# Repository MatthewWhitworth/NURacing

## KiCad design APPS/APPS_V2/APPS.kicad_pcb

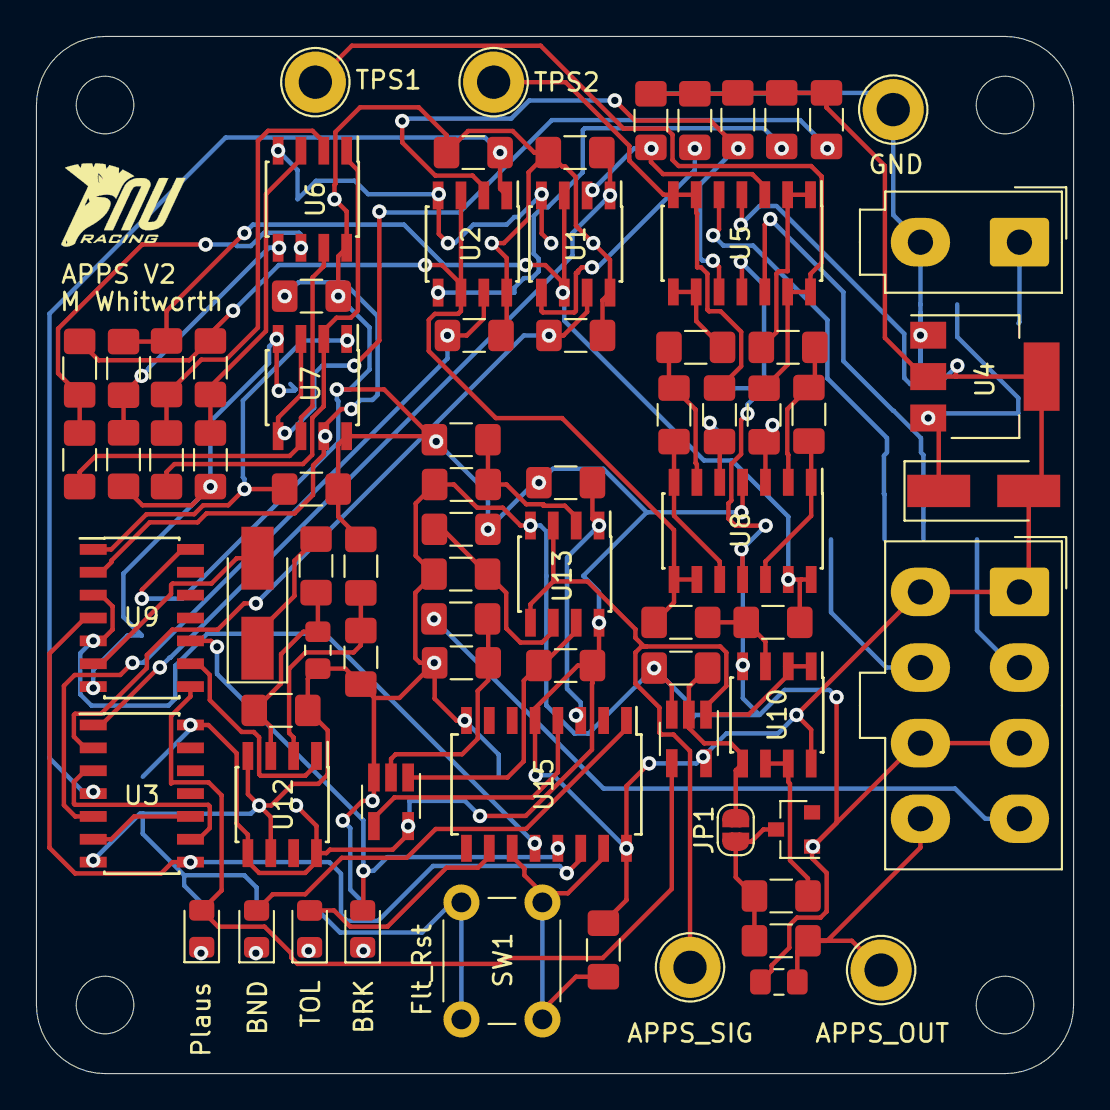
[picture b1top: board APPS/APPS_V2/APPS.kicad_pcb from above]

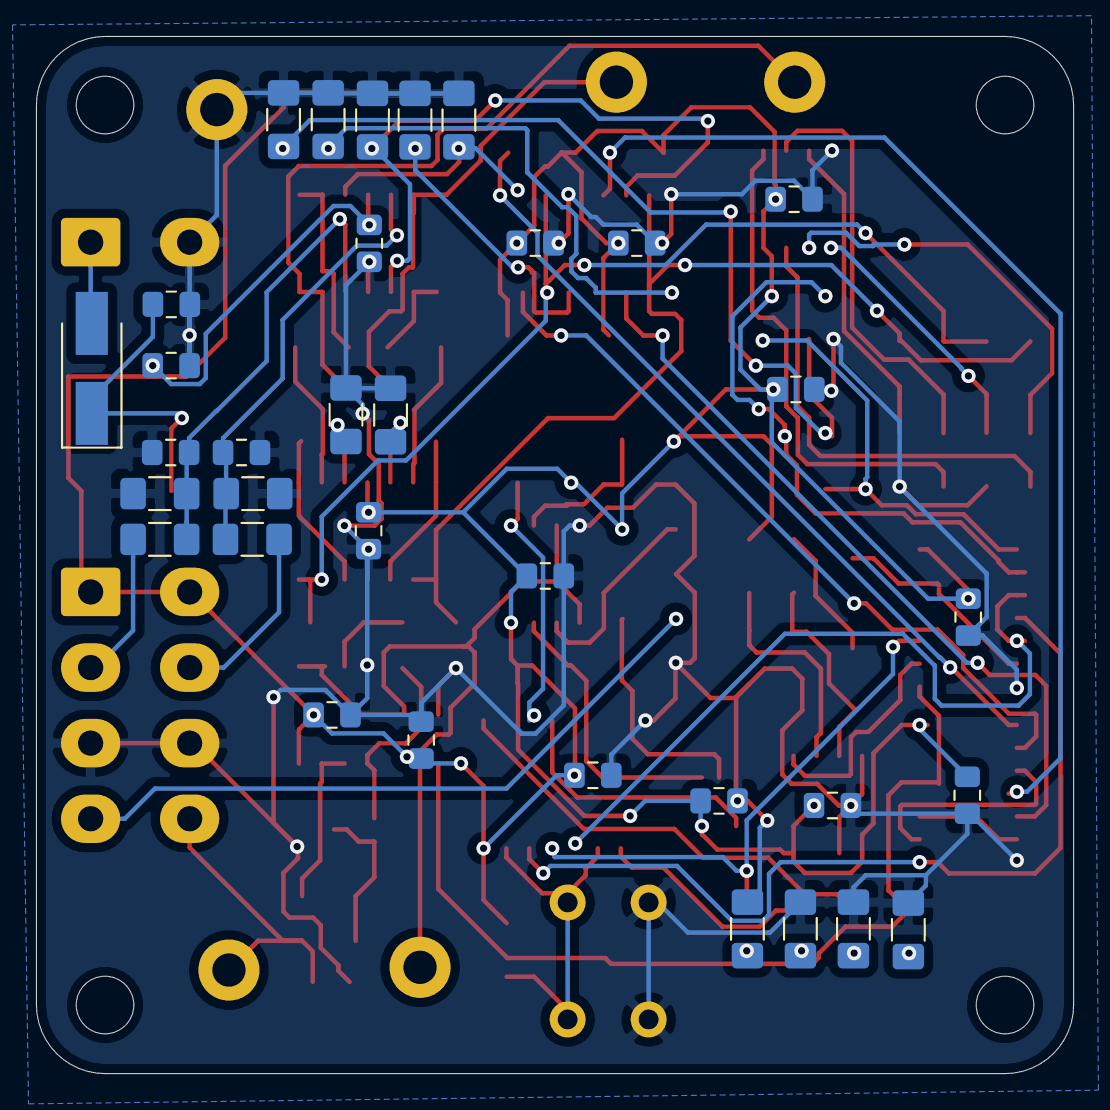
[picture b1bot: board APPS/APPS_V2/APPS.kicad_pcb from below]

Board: 2 copper layers, 57.6 x 57.6 mm, 110 parts (34 on the bottom side), 68 nets.

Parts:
C1, C2, C4, C6, C7, C8, C9, C10, C11, C12, C15, C16, C17, C18: 0.1uF; C_0805_2012Metric_Pad1.15x1.40mm_HandSolder
C3, C5: 10uF; C_0805_2012Metric_Pad1.15x1.40mm_HandSolder
C13: 2.2uF; C_0805_2012Metric_Pad1.15x1.40mm_HandSolder
C14: 47pF; C_0805_2012Metric_Pad1.15x1.40mm_HandSolder
C19, C20: C; C_0805_2012Metric_Pad1.15x1.40mm_HandSolder
D1, D2, D3: D; D_SMA_Handsoldering
D4: Plaus; LED_0805_2012Metric_Pad1.15x1.40mm_HandSolder
D6: D_Zener; D_SOT-23_ANK
D7: BRK; LED_0805_2012Metric_Pad1.15x1.40mm_HandSolder
D8: TOL; LED_0805_2012Metric_Pad1.15x1.40mm_HandSolder
D9: BND; LED_0805_2012Metric_Pad1.15x1.40mm_HandSolder
J1: Conn_01x08_Female; Molex_Mini-Fit_Jr_5566-08A_2x04_P4.20mm_Vertical
J2: Conn_01x02_Female; Molex_Mini-Fit_Jr_5566-02A_2x01_P4.20mm_Vertical
JP1: SolderJumper_2_Open; SolderJumper-2_P1.3mm_Open_RoundedPad1.0x1.5mm
R1, R2, R3, R4, R5, R6, R11, R12, R13, R14, R31, R47, R48, R49, R50: R; R_1206_3216Metric_Pad1.42x1.75mm_HandSolder
R7, R8, R9, R10, R15, R16, R17, R18, R19, R20, R21, R22, R23, R24, R25, R26, R30, R40, R41, R46: 10k; R_1206_3216Metric_Pad1.42x1.75mm_HandSolder
R27: 2k; R_1206_3216Metric_Pad1.42x1.75mm_HandSolder
R28, R35: 20k; R_1206_3216Metric_Pad1.42x1.75mm_HandSolder
R29: 100k; R_1206_3216Metric_Pad1.42x1.75mm_HandSolder
R32: 330; R_1206_3216Metric_Pad1.42x1.75mm_HandSolder
R33, R43, R44, R45: 470; R_1206_3216Metric_Pad1.42x1.75mm_HandSolder
R34: 10; R_1206_3216Metric_Pad1.42x1.75mm_HandSolder
R36: 3k; R_1206_3216Metric_Pad1.42x1.75mm_HandSolder
R37: 1.05k; R_1206_3216Metric_Pad1.42x1.75mm_HandSolder
R38: 1k; R_1206_3216Metric_Pad1.42x1.75mm_HandSolder
R39: 6.8k; R_1206_3216Metric_Pad1.42x1.75mm_HandSolder
R42: 4.7k; R_1206_3216Metric_Pad1.42x1.75mm_HandSolder
Rc1, Rc2: R; R_1206_3216Metric_Pad1.42x1.75mm_HandSolder
Rd1, Rd2: R; R_1206_3216Metric_Pad1.42x1.75mm_HandSolder
Re1, Re2: R; R_1206_3216Metric_Pad1.42x1.75mm_HandSolder
Rf1, Rf2: R; R_1206_3216Metric_Pad1.42x1.75mm_HandSolder
SW1: Flt_Rst; SW_PUSH_6mm
TP1: TPS1; TestPoint_Loop_D2.50mm_Drill1.85mm
TP2: TPS2; TestPoint_Loop_D2.50mm_Drill1.85mm
TP3: APPS_SIG; TestPoint_Loop_D2.50mm_Drill1.85mm
TP4: APPS_OUT; TestPoint_Loop_D2.50mm_Drill1.85mm
TP5: GND; TestPoint_Loop_D2.50mm_Drill1.85mm
U1, U2, U7, U13: LM393; SOIC-8_3.9x4.9mm_P1.27mm
U3, U9: 74LS08; SOIC-14_3.9x8.7mm_P1.27mm
U4: AP1117-50; SOT-223-3_TabPin2
U5, U8: MCP6004; SOIC-14_3.9x8.7mm_P1.27mm
U6, U10, U12: MCP6002-xSN; SOIC-8_3.9x4.9mm_P1.27mm
U11: Analog_Switch; SOT-23-5_HandSoldering
U14: 74LVC1G00; SOT-23-5_HandSoldering
U15: CD4044B; SOIC-16W_5.3x10.2mm_P1.27mm

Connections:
+12V: C3.1, D1.1, D2.1, U4.3
/APPS_OUT: C14.1, J1.8, R34.1, TP4.1
/APPS_SIG: TP3.1, U10.1, U10.2, U11.1, U13.3, U13.5
/BND_FLT: U3.8, U9.4, U15.14
/BRK_FLT: D7.2, U9.10, U15.13
/BRK_IN: J1.4, R39.2
/TOL_FLT: U9.3, U9.5, U15.12
/TPS_1: R16.2, R17.2, R25.2, U1.3, U1.6, U8.13, U8.14
/TPS_1_IN: J1.2, R48.2
/TPS_2: R15.2, R18.2, R26.2, U2.3, U2.6, U8.8, U8.9
/TPS_2_IN: J1.6, R47.2
/Tolerance: R13.2, R14.1, U7.3, U7.5
/Vmax_1: R3.2, R4.1, U1.5
/Vmax_2: R11.2, R12.1, U2.5
/Vmin_1: R1.2, R2.1, U1.2, U5.3
/Vmin_2: R5.2, R6.1, U2.2, U5.10
GND: C1.2, C2.2, C3.2, C4.2, C5.2, C6.2, C7.2, C8.2, C9.2, C10.2, C11.2, C12.2, C13.2, C14.2, C15.2, C16.2, C17.2, C18.2, C19.2, C20.2, D6.2, J1.3, J1.7, J2.2, R2.2, R4.2, R6.2, R12.2, R14.2, R19.2, R20.2, R28.1, R30.2, R31.2, R33.1, R37.2, R38.2, R42.2, R43.1, R44.1, R45.2, R49.2, R50.2, Rc1.1, Rc2.1, SW1.2, TP5.1, U1.4, U2.4, U3.7, U4.1, U5.11, U6.4, U7.4, U8.11, U9.7, U10.4, U11.3, U12.4, U12.6, U13.4, U14.3, U15.8
unnamed: C13.1, R27.1, R28.2, U12.3
unnamed: C19.1, R47.1, R49.1, U5.5
unnamed: C20.1, R48.1, R50.1, U5.12
unnamed: D1.2, J2.1
unnamed: D3.1, R27.2
unnamed: D3.2, U9.6
unnamed: D4.1, R33.2
unnamed: D4.2, U9.8, U11.4
unnamed: D6.1, JP1.2, R32.1, R34.2
unnamed: D7.1, R43.2
unnamed: D8.1, R44.2
unnamed: D8.2, U15.10
unnamed: D9.1, R45.1
unnamed: D9.2, U15.1
unnamed: JP1.1, R31.1, U10.5, U11.2
unnamed: R7.2, U1.1, U3.1
unnamed: R8.1, U1.7, U3.2
unnamed: R9.2, U2.1, U3.4
unnamed: R10.2, U2.7, U3.5
unnamed: R15.1, R19.1, U6.3
unnamed: R16.1, R21.1, U6.2
unnamed: R17.1, R20.1, U6.5
unnamed: R18.1, R22.1, U6.6
unnamed: R21.2, U6.1, U7.2
unnamed: R22.2, U6.7, U7.6
unnamed: R23.2, U7.1, U9.1
unnamed: R24.1, U7.7, U9.2
unnamed: R25.1, R26.1, U10.3
unnamed: R29.1, R30.1, U12.2
unnamed: R32.2, U10.6, U10.7
unnamed: R35.1, R37.1, U13.2
unnamed: R36.1, R38.1, U13.6
unnamed: R39.1, R42.1, U14.2
unnamed: R40.2, U13.1, U15.3
unnamed: R41.2, U13.7, U14.1
unnamed: R46.1, SW1.1, U15.11, U15.15
unnamed: Rc1.2, Rd1.1, U8.3
unnamed: Rc2.2, Rd2.1, U8.5
unnamed: Rd1.2, TP1.1, U5.13, U5.14
unnamed: Rd2.2, TP2.1, U5.6, U5.7
unnamed: Re1.1, U5.1, U5.2
unnamed: Re1.2, Rf1.1, U8.2
unnamed: Re2.1, U5.8, U5.9
unnamed: Re2.2, Rf2.1, U8.6
unnamed: Rf1.2, U8.1, U8.12
unnamed: Rf2.2, U8.7, U8.10
unnamed: U3.3, U3.9
unnamed: U3.6, U3.10
unnamed: U9.9, U12.1
unnamed: U14.4, U15.4
VCC: C1.1, C2.1, C4.1, C5.1, C6.1, C7.1, C8.1, C9.1, C10.1, C11.1, C12.1, C15.1, C16.1, C17.1, C18.1, D2.2, J1.1, J1.5, R1.1, R3.1, R5.1, R7.1, R8.2, R9.1, R10.1, R11.1, R13.1, R23.1, R24.2, R29.2, R35.2, R36.2, R40.1, R41.1, R46.2, U1.8, U2.8, U3.14, U4.2, U5.4, U6.8, U7.8, U8.4, U9.14, U10.8, U11.5, U12.5, U12.8, U13.8, U14.5, U15.5, U15.16

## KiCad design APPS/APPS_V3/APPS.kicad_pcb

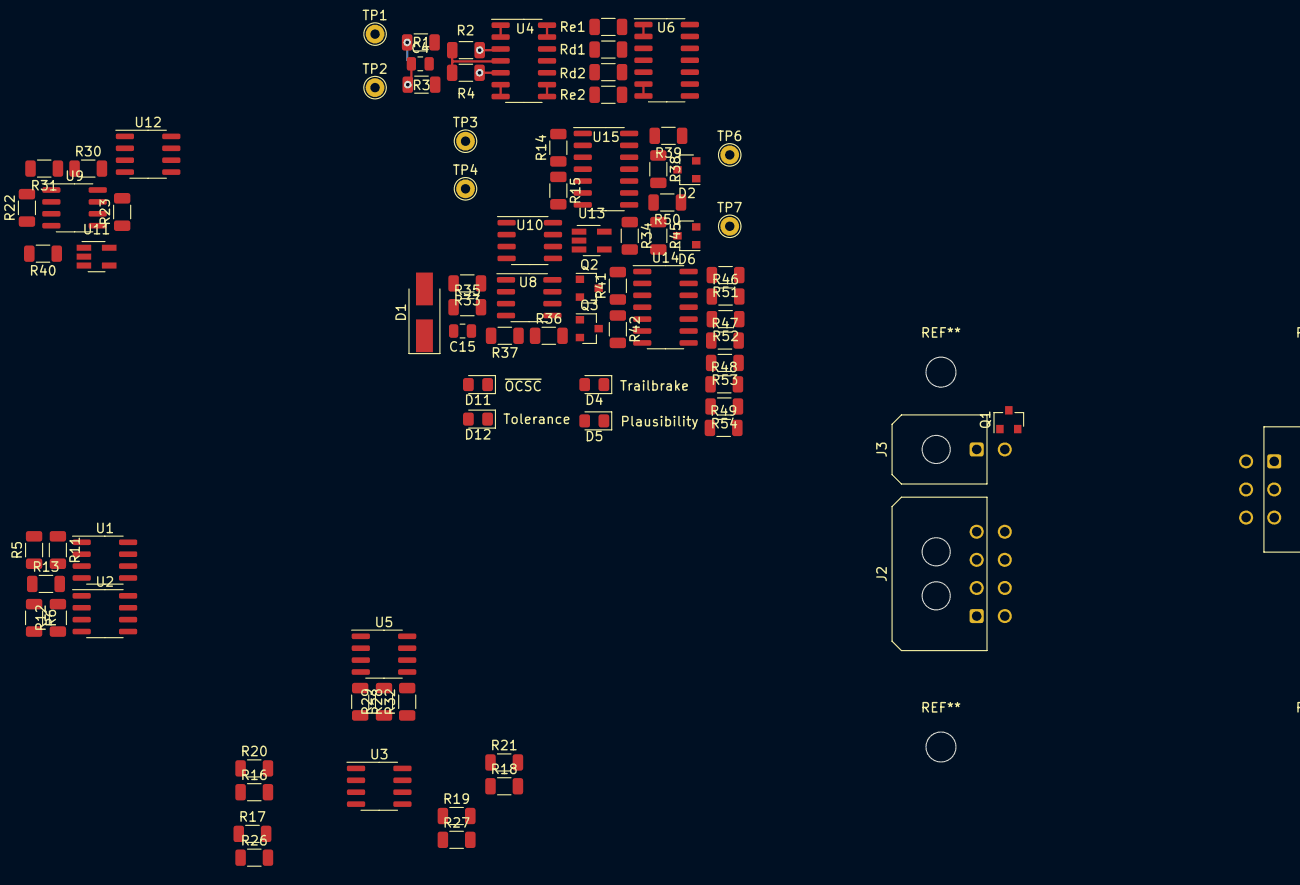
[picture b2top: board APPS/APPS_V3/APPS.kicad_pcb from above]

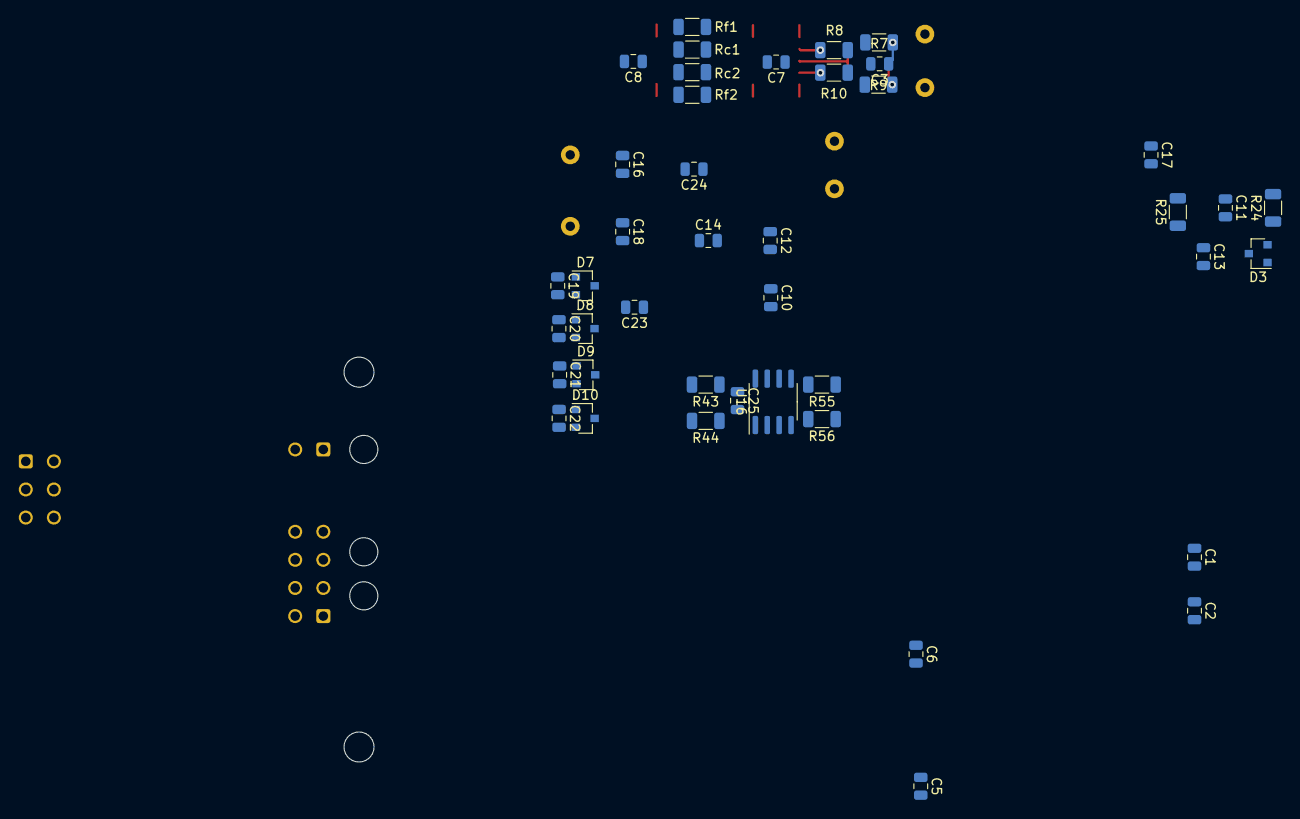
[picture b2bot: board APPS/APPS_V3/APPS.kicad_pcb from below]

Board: 2 copper layers, 127 parts (42 on the bottom side), 75 nets.

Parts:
C1, C2, C5, C6, C7, C8, C10, C11, C12, C13, C14, C23, C24, C25: 0.1uF; C_0805_2012Metric
C3, C4: C; C_0805_2012Metric
C15: 2.2uF; C_0805_2012Metric
C16, C18, C19, C20, C21, C22: 47pF; C_0805_2012Metric
C17: CP1_Small; C_0805_2012Metric
D1: D; D_SMA_Handsoldering
D2, D6, D7, D8, D9, D10: D_Zener; D_SOT-23_ANK
D3: D_Zener-Device; D_SOT-23_ANK
D4: Trailbrake; LED_0805_2012Metric_Pad1.15x1.40mm_HandSolder
D5: Plausibility; LED_0805_2012Metric_Pad1.15x1.40mm_HandSolder
D11: ~OCSC; LED_0805_2012Metric_Pad1.15x1.40mm_HandSolder
D12: Tolerance; LED_0805_2012Metric_Pad1.15x1.40mm_HandSolder
J1: Conn_01x06_Female; Molex_Micro-Fit_3.0_43045-0600_2x03_P3.00mm_Horizontal
J2: Conn_01x08_Female; Molex_Micro-Fit_3.0_43045-0800_2x04_P3.00mm_Horizontal
J3: Conn_01x02_Female; Molex_Micro-Fit_3.0_43045-0200_2x01_P3.00mm_Horizontal
Q1: Q_PMOS_DGS; SOT-23
Q2, Q3: 2N7002; SOT-23
R1, R3, R7, R9, R34, R41, R42, R43, R44, R55, R56: R; R_1206_3216Metric
R2: 39k; R_1206_3216Metric
R4: 33k; R_1206_3216Metric
R5, R12, R36, R37: 100k; R_1206_3216Metric
R6, R11, R13, R14, R15, R16, R17, R18, R19, R20, R21, R26, R27, R28, R30, R31, R32: 10k; R_1206_3216Metric
R8: 9.1k; R_1206_3216Metric
R10: 15k; R_1206_3216Metric
R22: 3k; R_1206_3216Metric
R23, R35: 20k; R_1206_3216Metric
R24: 1k; R_1206_3216Metric
R25: 1.05k; R_1206_3216Metric
R29: 200k; R_1206_3216Metric
R33: 2k; R_1206_3216Metric
R38, R45, R46, R47, R48, R49: 330; R_1206_3216Metric
R39, R50, R51, R52, R53, R54: 10; R_1206_3216Metric
R40: R-Device; R_1206_3216Metric
Rc1, Rc2: R; R_1206_3216Metric
Rd1, Rd2: R; R_1206_3216Metric
Re1, Re2: R; R_1206_3216Metric
Rf1, Rf2: R; R_1206_3216Metric
TP1: TPS1_IN; TestPoint_THTPad_D2.0mm_Drill1.0mm
TP2: TPS2_IN; TestPoint_THTPad_D2.0mm_Drill1.0mm
TP3, TP4, TP6, TP7: TestPoint; TestPoint_THTPad_D2.0mm_Drill1.0mm
U1, U2, U5, U9: LM393; SOIC-8_3.9x4.9mm_P1.27mm
U3, U8, U16: MCP6002-xSN; SOIC-8_3.9x4.9mm_P1.27mm
U4, U6, U14, U15: MCP6004; SOIC-14_3.9x8.7mm_P1.27mm
U10: 74AUC2G08; SOIC-8_3.9x4.9mm_P1.27mm
U11: 74LVC1G00; SOT-23-5_HandSoldering
U12: LM555; SOIC-8_3.9x4.9mm_P1.27mm
U13: Analog_Switch; SOT-23-5_HandSoldering

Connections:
+5V: J3.1, Q1.1
/APPS_OUT_1: C16.1, J1.1, R39.1, TP6.1
/APPS_OUT_2: C18.1, J1.2, R50.1, TP7.1
/APPS_SIG: U9.3, U9.5, U13.1, U15.6, U15.7
/BND_FLT: R13.2, U1.1, U1.7, U2.1, U2.7, U10.5, U16.3
/BRK: D3.1, R40.1, U11.1
/BRK_IN: J2.7, R40.2
/OC: R5.2, R11.1, U1.3, U1.5
/PLAUS: C21.1, J1.5, R53.1
/PLAUSIBILITY: Q3.1, U8.1, U10.2, U14.10
/SC: R6.2, R12.1, U2.2, U2.6
/TOL_FLT: R32.2, U5.1, U5.7, U10.6, U16.5
/TPS_1: R14.2, R17.2, R18.2, TP3.1, U6.1, U6.2
/TPS_1_IN: J2.5, R1.2, TP1.1
/TPS_1_RAW: C3.1, R1.1, R7.1, U1.2, U2.3, U4.12
/TPS_2: R15.2, R16.2, R19.2, TP4.1, U6.6, U6.7
/TPS_2_IN: J2.6, R3.2, TP2.1
/TPS_2_RAW: C4.1, R3.1, R9.1, U1.6, U2.5, U4.10
/TRAIL: C19.1, J1.3, R51.1
/TRAILBRAKE: Q2.1, U10.1, U12.3, U14.12
/Tolerance: R28.1, R29.2, U5.3, U5.5
/Vmin_1: R2.2, R8.1, U4.3
/Vmin_2: R4.2, R10.1, U4.5
/~PLAUS: C22.1, J1.6, R54.1
/~TRAIL: C20.1, J1.4, R52.1
GND: C1.2, C2.2, C3.2, C4.2, C5.2, C6.2, C7.2, C8.2, C10.2, C11.2, C12.2, C13.2, C14.2, C15.2, C16.2, C17.2, C18.2, C19.2, C20.2, C21.2, C22.2, C23.2, C24.2, C25.2, D2.2, D3.2, D6.2, D7.2, D8.2, D9.2, D10.2, J2.3, J2.4, J3.2, Q1.2, Q2.2, Q3.2, R7.2, R8.2, R9.2, R10.2, R11.2, R12.2, R20.2, R21.2, R24.2, R25.2, R28.2, R34.2, R35.1, R37.2, R43.1, R44.1, R55.1, R56.1, Rc1.1, Rc2.1, U1.4, U2.4, U3.4, U4.11, U5.4, U6.11, U8.4, U8.6, U9.4, U10.4, U11.3, U12.1, U12.6, U13.3, U14.11, U15.2, U15.11, U16.4
unnamed: C15.1, R33.1, R35.2, U8.3
unnamed: D1.1, R33.2
unnamed: D1.2, U10.3
unnamed: D2.1, R38.1, R39.2
unnamed: D4.1, R43.2
unnamed: D4.2, R46.2, U14.13, U14.14
unnamed: D5.1, R44.2
unnamed: D5.2, R48.2, U14.8, U14.9
unnamed: D6.1, R45.1, R50.2
unnamed: D7.1, R46.1, R51.2
unnamed: D8.1, R47.1, R52.2
unnamed: D9.1, R48.1, R53.2
unnamed: D10.1, R49.1, R54.2
unnamed: D11.1, R55.2
unnamed: D11.2, U16.1, U16.2
unnamed: D12.1, R56.2
unnamed: D12.2, U16.6, U16.7
unnamed: Q2.3, R41.2, U14.3
unnamed: Q3.3, R42.2, U14.5
unnamed: R14.1, R15.1, U15.5
unnamed: R16.1, R20.1, U3.3
unnamed: R17.1, R26.1, U3.2
unnamed: R18.1, R21.1, U3.5
unnamed: R19.1, R27.1, U3.6
unnamed: R22.1, R24.1, U9.2
unnamed: R23.1, R25.1, U9.6
unnamed: R26.2, U3.1, U5.2
unnamed: R27.2, U3.7, U5.6
unnamed: R30.2, U9.7, U12.2
unnamed: R31.2, U9.1, U11.2
unnamed: R34.1, U13.2, U15.10, U15.12
unnamed: R36.1, R37.1, U8.2
unnamed: R38.2, U15.13, U15.14
unnamed: R45.2, U15.8, U15.9
unnamed: R47.2, U14.1, U14.2
unnamed: R49.2, U14.6, U14.7
unnamed: Rc1.2, Rd1.1, U6.12
unnamed: Rc2.2, Rd2.1, U6.10
unnamed: Rd1.2, U4.13, U4.14
unnamed: Rd2.2, U4.8, U4.9
unnamed: Re1.1, U4.1, U4.2
unnamed: Re1.2, Rf1.1, U6.13
unnamed: Re2.1, U4.6, U4.7
unnamed: Re2.2, Rf2.1, U6.9
unnamed: Rf1.2, U6.3, U6.14
unnamed: Rf2.2, U6.5, U6.8
unnamed: U10.7, U13.4
unnamed: U11.4, U12.4
VCC: C1.1, C2.1, C5.1, C6.1, C7.1, C8.1, C10.1, C11.1, C12.1, C13.1, C14.1, C17.1, C23.1, C24.1, C25.1, J2.1, J2.2, Q1.3, R2.1, R4.1, R5.1, R6.1, R13.1, R22.2, R23.2, R29.1, R30.1, R31.1, R32.1, R36.2, R41.1, R42.1, U1.8, U2.8, U3.8, U4.4, U5.8, U6.4, U8.5, U8.8, U9.8, U10.8, U11.5, U12.8, U13.5, U14.4, U15.3, U15.4, U16.8

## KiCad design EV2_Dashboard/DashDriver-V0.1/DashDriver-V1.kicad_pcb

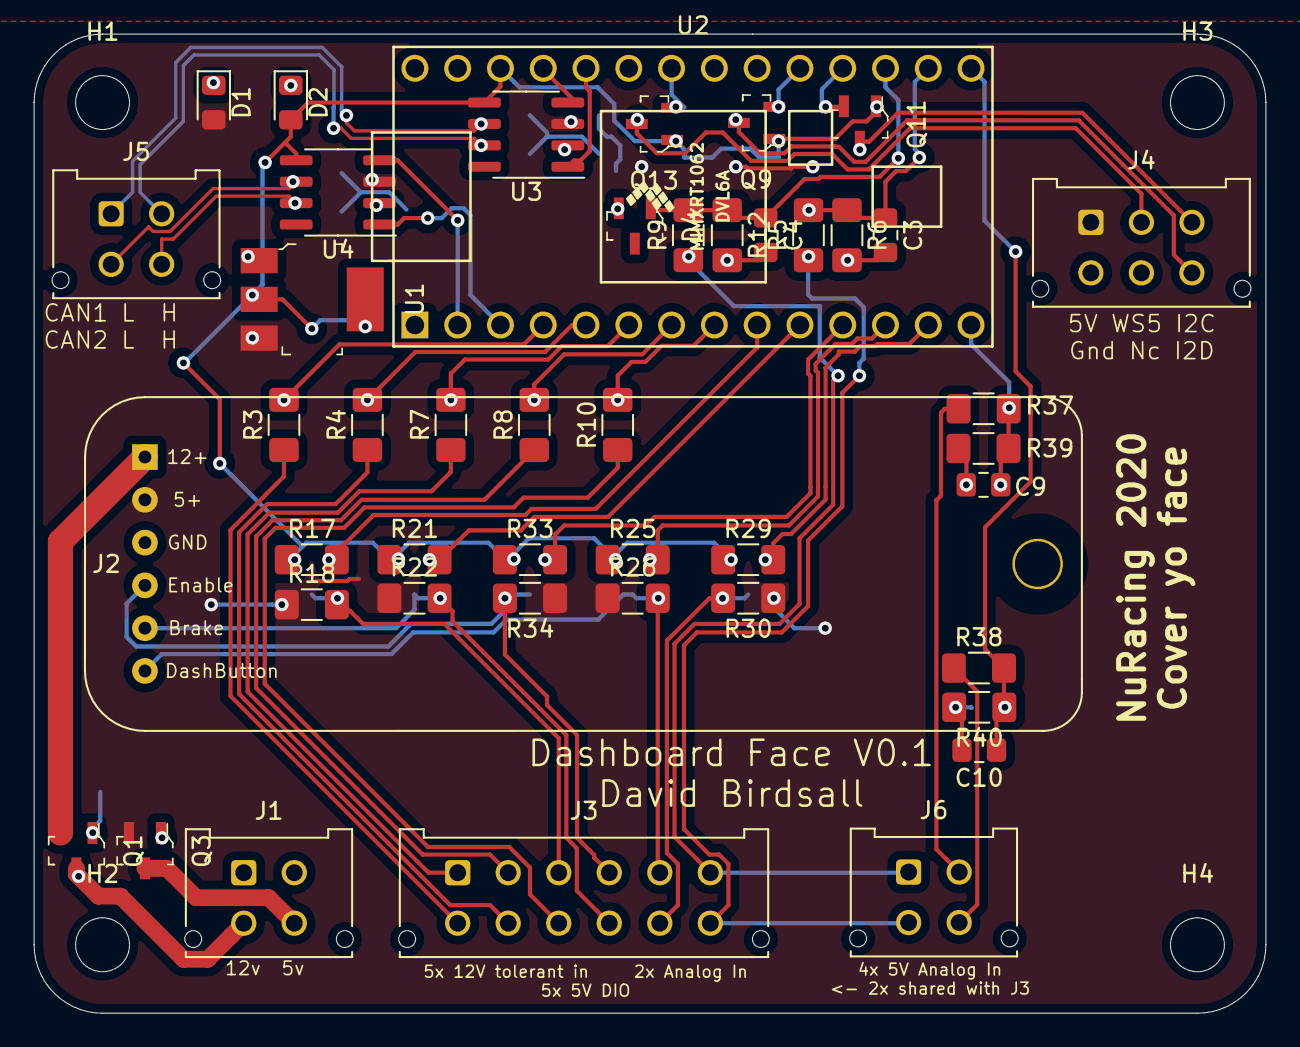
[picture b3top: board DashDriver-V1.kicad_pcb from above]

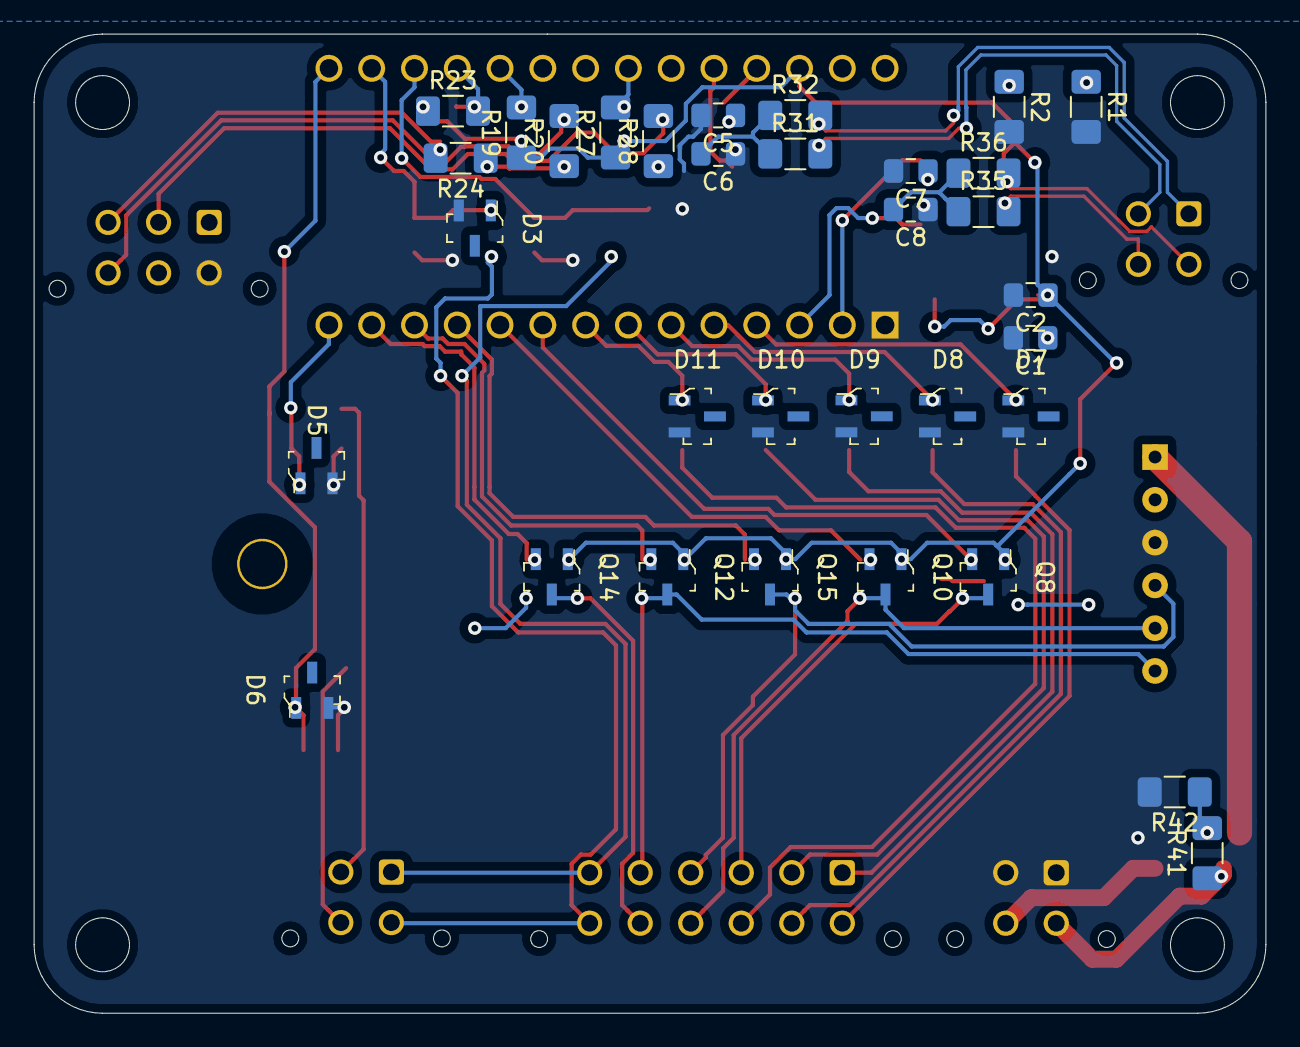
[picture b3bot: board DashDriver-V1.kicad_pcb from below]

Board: 2 copper layers, 73.1 x 58.1 mm, 82 parts (33 on the bottom side), 53 nets.

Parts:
C1, C2: C; C_0805_2012Metric_Pad1.15x1.40mm_HandSolder
C3, C4, C9, C10: 10n; C_0805_2012Metric_Pad1.15x1.40mm_HandSolder
C5, C7: 100n; C_0805_2012Metric_Pad1.15x1.40mm_HandSolder
C6, C8: 50n; C_0805_2012Metric_Pad1.15x1.40mm_HandSolder
D1, D2: LED; D_0805_2012Metric_Pad1.15x1.40mm_HandSolder
D3, D4, D5, D6, D7, D8, D9, D10, D11: D_Zener; SOT-23-3
H1, H2, H3, H4: MountingHole; MountingHole_3.2mm_M3
J1: Power; Molex_Micro-Fit_3.0_43045-0412_2x02_P3.00mm_Vertical
J2: RTD_Daughter; RTD-Daughter
J3: MainIO; Molex_Micro-Fit_3.0_43045-1212_2x06_P3.00mm_Vertical
J4: Dash Conn; Molex_Micro-Fit_3.0_43045-0612_2x03_P3.00mm_Vertical
J5: CAN; Molex_Micro-Fit_3.0_43045-0412_2x02_P3.00mm_Vertical
J6: Analog 0-5V; Molex_Micro-Fit_3.0_43045-0412_2x02_P3.00mm_Vertical
Q1, Q3: AO3401A; SOT-23-3
Q8, Q9, Q10, Q11, Q12, Q13, Q14, Q15: 2N7002; SOT-23-3
R1, R20, R24, R28: 1k; R_1206_3216Metric_Pad1.42x1.75mm_HandSolder
R2: 250; R_1206_3216Metric_Pad1.42x1.75mm_HandSolder
R3, R4, R7, R8, R10, R17, R18, R19, R21, R22, R23, R25, R26, R27, R29, R30, R33, R34, R41, R42: 10k; R_1206_3216Metric_Pad1.42x1.75mm_HandSolder
R5, R9, R37, R38: 10k3; R_1206_3216Metric_Pad1.42x1.75mm_HandSolder
R6, R12, R39, R40: 20k; R_1206_3216Metric_Pad1.42x1.75mm_HandSolder
R31, R32, R35, R36: 60; R_1206_3216Metric_Pad1.42x1.75mm_HandSolder
U1: LM1117MPX-3_3_NOPB; SOT-223
U2: Teensy4.0; Teensy40
U3, U4: TJA1051T-3; SOIC-8_3.9x4.9mm_P1.27mm

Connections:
/+3V3: C2.1, D2.2, Q8.1, Q9.1, Q10.1, Q11.1, Q12.1, Q13.1, Q14.1, Q15.1, R17.1, R19.1, R21.1, R23.1, R25.1, R27.1, R29.1, R33.1, U1.2, U1.4, U2.31, U3.5, U4.5
/+5V: C1.1, C5.1, C7.1, D1.2, J2.2, J4.1, Q3.2, R18.1, R20.1, R22.1, R24.1, R26.1, R28.1, R30.1, R34.1, U1.3, U3.3, U4.3
/+12V: J2.1, Q1.2
/AIn_Spare: C4.1, D4.1, R9.2, R12.1, U2.22
/AIn_Spare_: J3.6, J6.1, R9.1
/APPS_Bound: D11.1, R10.2, U2.8
/APPS_Bound_: J3.9, R10.1
/APPS_Dis: Q8.2, R17.2, U2.9
/APPS_Dis_: J3.3, Q8.3, R18.2
/APPS_Trail: D10.1, R8.2, U2.7
/APPS_Trail_: J3.2, R8.1
/Brake_Sw: Q10.2, R21.2, U2.10
/Brake_Sw_: J2.5, J3.10, Q10.3, R22.2
/BrkPrs_F: C9.1, D5.1, R37.2, R39.1, U2.14
/BrkPrs_F_: J6.2, R37.1
/BrkPrs_R: C10.1, D6.1, R38.2, R40.1, U2.20
/BrkPrs_R_: J6.4, R38.1
/C1+: J5.2, R31.2, U3.7
/C1-: J5.1, R32.2, U3.6
/C2+: J5.4, R35.2, U4.7
/C2-: J5.3, R36.2, U4.6
/CRX1: U2.30, U3.4
/CRX2: U2.2, U4.4
/CTX1: U2.29, U3.1
/CTX2: U2.3, U4.1
/I2C_C: Q11.2, R23.2, U2.23
/I2C_C-5V: J4.3, Q11.3, R24.2
/I2C_D: Q9.2, R19.2, U2.24
/I2C_D-5V: J4.6, Q9.3, R20.2
/LED_Data: Q13.2, R27.2, U2.27
/LED_Data-5V: J4.2, Q13.3, R28.2
/RTD_Gate: Q15.2, R33.2, U2.11
/RTD_Gate_: J2.4, J3.4, Q15.3, R34.2
/SD_BOTS: D8.1, R4.2, U2.5
/SD_BOTS_: J3.8, R4.1
/SD_Dash: D9.1, R7.2, U2.6
/SD_Dash_: J3.1, R7.1
/SD_Inertia: D7.1, R3.2, U2.4
/SD_Inertia_: J3.7, R3.1
/Spare_D2: Q12.2, R25.2, U2.12
/Spare_D2_: J2.6, J3.5, Q12.3, R26.2
/Spare_D3: Q14.2, R29.2, U2.13
/Spare_D3_: J3.11, Q14.3, R30.2
/Throttle_Pos: C3.1, D3.1, R5.2, R6.1, U2.21
/Throttle_Pos_: J3.12, J6.3, R5.1
GND: C1.2, C2.2, C3.2, C4.2, C5.2, C6.1, C7.2, C8.1, C9.2, C10.2, D3.2, D4.2, D5.2, D6.2, D7.2, D8.2, D9.2, D10.2, D11.2, J1.1, J1.2, J2.3, J4.4, Q3.1, R1.2, R2.2, R6.2, R12.2, R39.2, R40.2, R42.2, U1.1, U2.1, U3.2, U4.2
unnamed: C6.2, R31.1, R32.1
unnamed: C8.2, R35.1, R36.1
unnamed: D1.1, R1.1
unnamed: D2.1, R2.1
unnamed: J1.3, Q1.3, R41.1
unnamed: J1.4, Q3.3
unnamed: Q1.1, R41.2, R42.1
